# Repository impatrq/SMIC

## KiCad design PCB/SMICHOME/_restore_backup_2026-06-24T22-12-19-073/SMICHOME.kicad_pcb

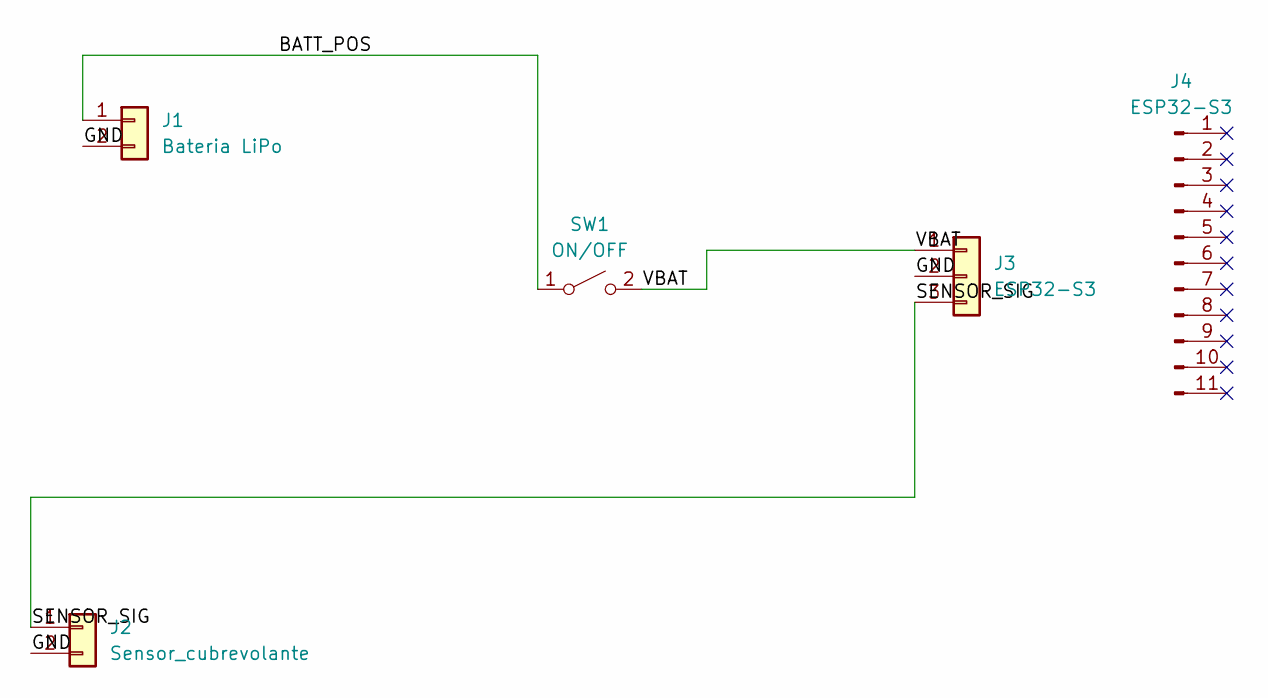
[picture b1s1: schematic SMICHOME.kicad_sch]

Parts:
J1: Bateria LiPo; JST_PH_B2B-PH-K_1x02_P2.00mm_Vertical
J2: Sensor_cubrevolante; JST_PH_B2B-PH-K_1x02_P2.00mm_Vertical
J3, J4: ESP32-S3; PinSocket_1x11_P2.54mm_Vertical
SW1: ON/OFF; SW_Slide_SPDT_Straight_CK_OS102011MS2Q

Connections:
/BATT_POS: J1.1, SW1.1 (A)
/GND: J1.2, J2.2, J3.2
/SENSOR_SIG: J2.1, J3.3
/VBAT: J3.1, SW1.2 (B)

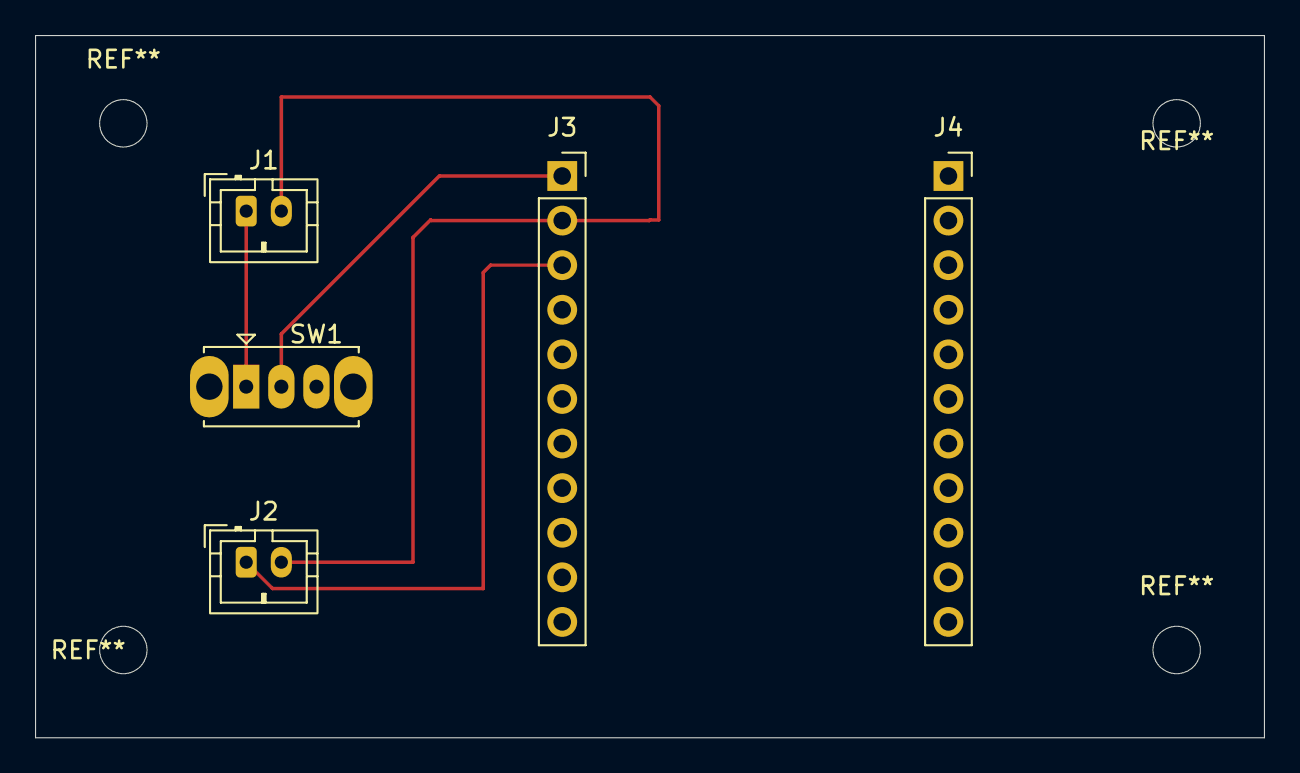
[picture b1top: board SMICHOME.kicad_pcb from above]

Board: 2 copper layers, 70.0 x 40.0 mm, 5 parts (0 on the bottom side), 4 nets.

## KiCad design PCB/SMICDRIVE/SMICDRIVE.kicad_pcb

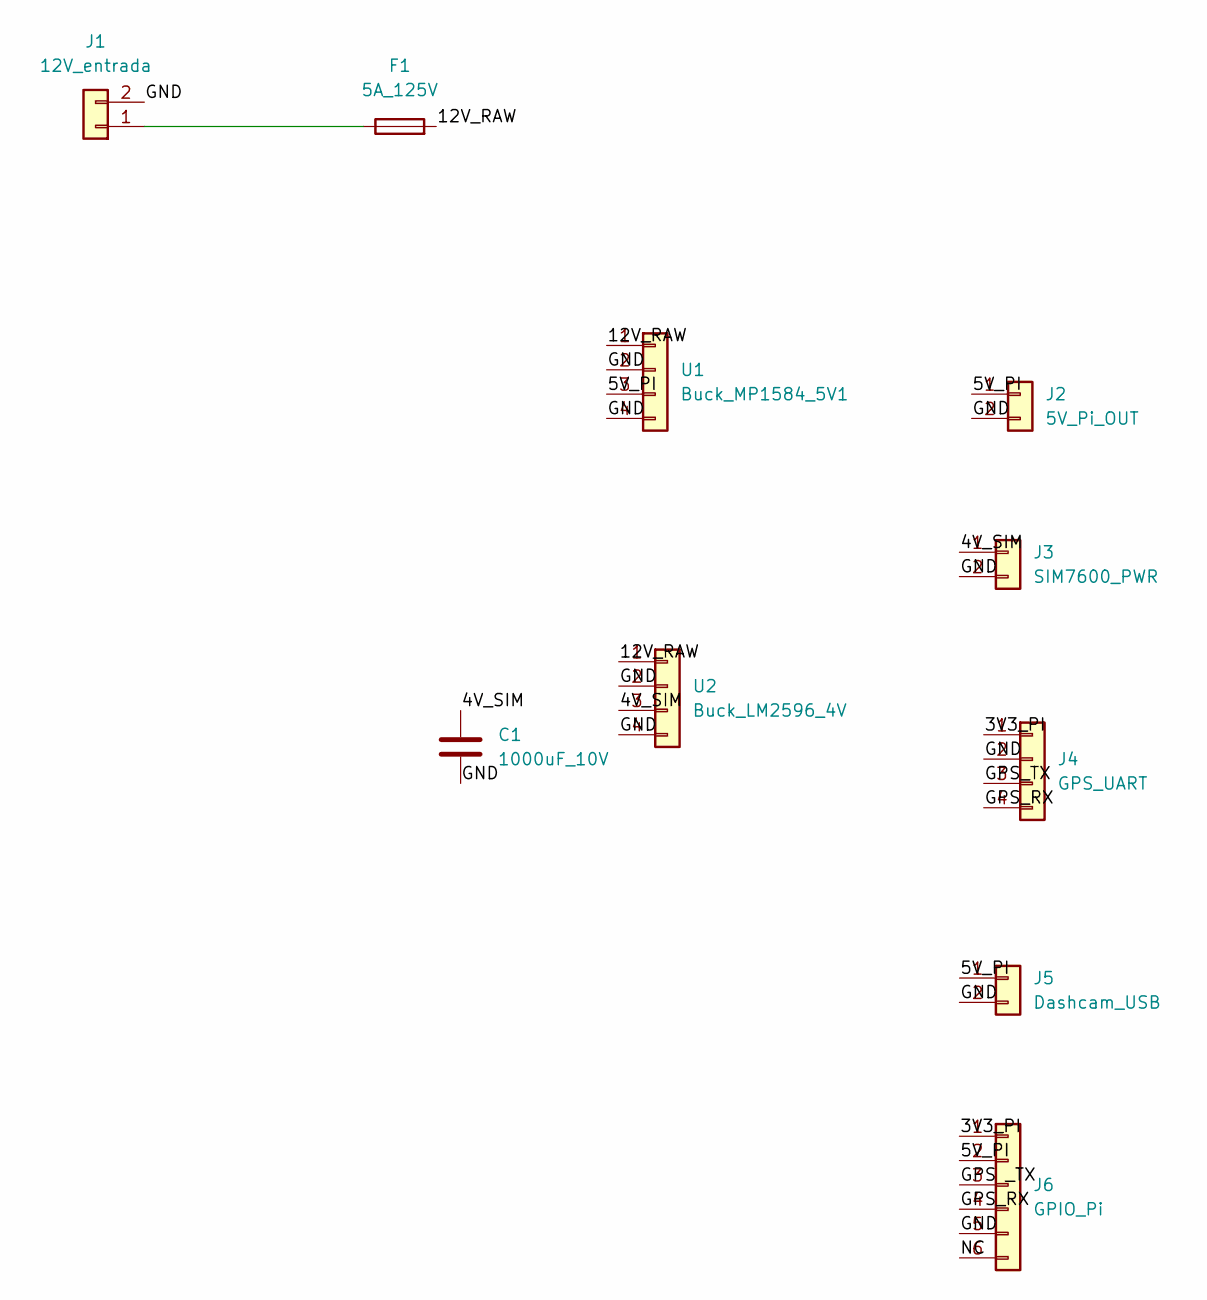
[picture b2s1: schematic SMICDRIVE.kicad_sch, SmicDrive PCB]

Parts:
C1: 1000uF_10V; CP_Radial_D10.0mm_P5.00mm
F1: 5A_125V; Fuse_Bourns_MF-RHT500
J1: 12V_entrada; TerminalBlock_Philmore_TB132_1x02_P5.00mm_Horizontal
J2: 5V_Pi_OUT; PinHeader_1x02_P2.54mm_Vertical
J3: SIM7600_PWR; JST_PH_S2B-PH-K_1x02_P2.00mm_Horizontal
J4: GPS_UART; JST_PH_S4B-PH-K_1x04_P2.00mm_Horizontal
J5: Dashcam_USB; USB_A_Stewart_SS-52100-001_Horizontal
J6: GPIO_Pi; PinHeader_1x06_P2.54mm_Vertical
U1: Buck_MP1584_5V1; PinHeader_1x04_P2.54mm_Vertical
U2: Buck_LM2596_4V; PinHeader_1x04_P2.54mm_Vertical

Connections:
/3V3_PI: J4.1, J6.1
/4V_SIM: C1.1, J3.1, U2.3
/5V_PI: J2.1, J5.1, J6.2, U1.3
/12V_RAW: F1.2, U1.1, U2.1
/GND: C1.2, J1.2, J2.2, J3.2, J4.2, J5.2, J6.5, U1.2, U1.4, U2.2, U2.4
/GPS _TX: J6.3
/GPS_RX: J4.4, J6.4
/GPS_TX: J4.3
/NC: J6.6
unnamed: F1.1, J1.1

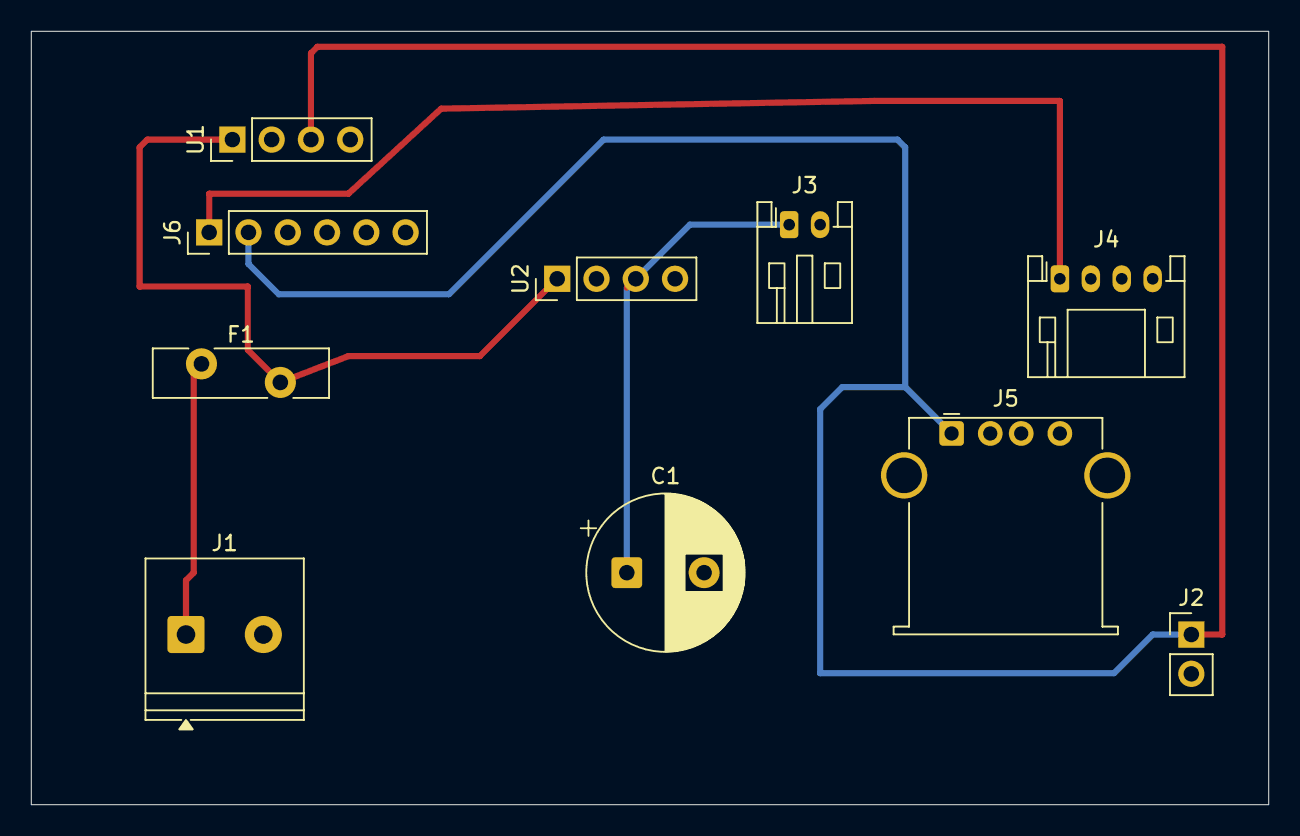
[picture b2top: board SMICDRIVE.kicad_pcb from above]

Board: 2 copper layers, 80.0 x 50.0 mm, 10 parts (0 on the bottom side), 7 nets.

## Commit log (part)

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2026-04-14 Create SMIC (1).pdf
    anteproyecto
2026-04-16 Estructura inicial, modulo sensores y documentacion PDF
2026-04-16 Eliminar carpeta sensores - no se utilizara en el proyecto
2026-04-16 Agregar deteccion.py y carpeta de campo 16/04
2026-04-17 Distraccion.py y CameraModule2 17/4
2026-04-21 CAMBIOS 21/4 y Descripcion de funcionamiento general del sistema
2026-04-22 historiasdeusuario
2026-04-22 esp32pruebaysetup
2026-04-22 Sistema de alertas
2026-04-28 doc: agregar pdfSIM
2026-05-06 Avance distraccion.py y somnolencia.py
2026-05-15 prueba de sistema de clips
2026-06-02 ESP32: deep sleep 500ms con lectura touch capacitivo
2026-06-02 PDF ESP32 2/6
2026-06-10 Adaptar camara a Picamera2 RPi - buffer circular de eventos
2026-06-24 feat: servidor Flask SMIC - API REST y panel web
2026-06-24 feat: envio de eventos al servidor Flask via HTTP
2026-06-25 Documentacion PCB Carrier SMIC Home
2026-06-25 SmicDrive: esquemático y PCB KiCad + documentación
2026-06-25 documentacion SMICHome
2026-06-25 feat: sync endpoint, boton actualizar clips y logo SMIC
2026-06-25 feat: muestra de los videos grabados en rpi en la pagina web
